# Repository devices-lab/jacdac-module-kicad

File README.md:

# jacdac-template-kicad

Jacdac RGB module KiCad project files for use as a template when creating new Jacdac modules. 

Based on Altium schematics from the [jacdac-ddk](https://github.com/jacdac/jacdac-ddk) and the [Jacdac KiCad library](https://github.com/mac-aron/jacdac-kicad).

#### Usage
- The script `library/convert.sh` can be used to download component symbols and footprints from LCSC (JLCPCB).
- The jobfile `export-fab-files.kicad_jobset` generates fabrication files to `gerbers/` with the correct settings
  - The column names in the CPL (component placement list) are incorrect for JLCPCB

Check the [neopixel-gerbersockets](../../tree/neopixel-gerbersockets) branch for a version with GerberSockets added.

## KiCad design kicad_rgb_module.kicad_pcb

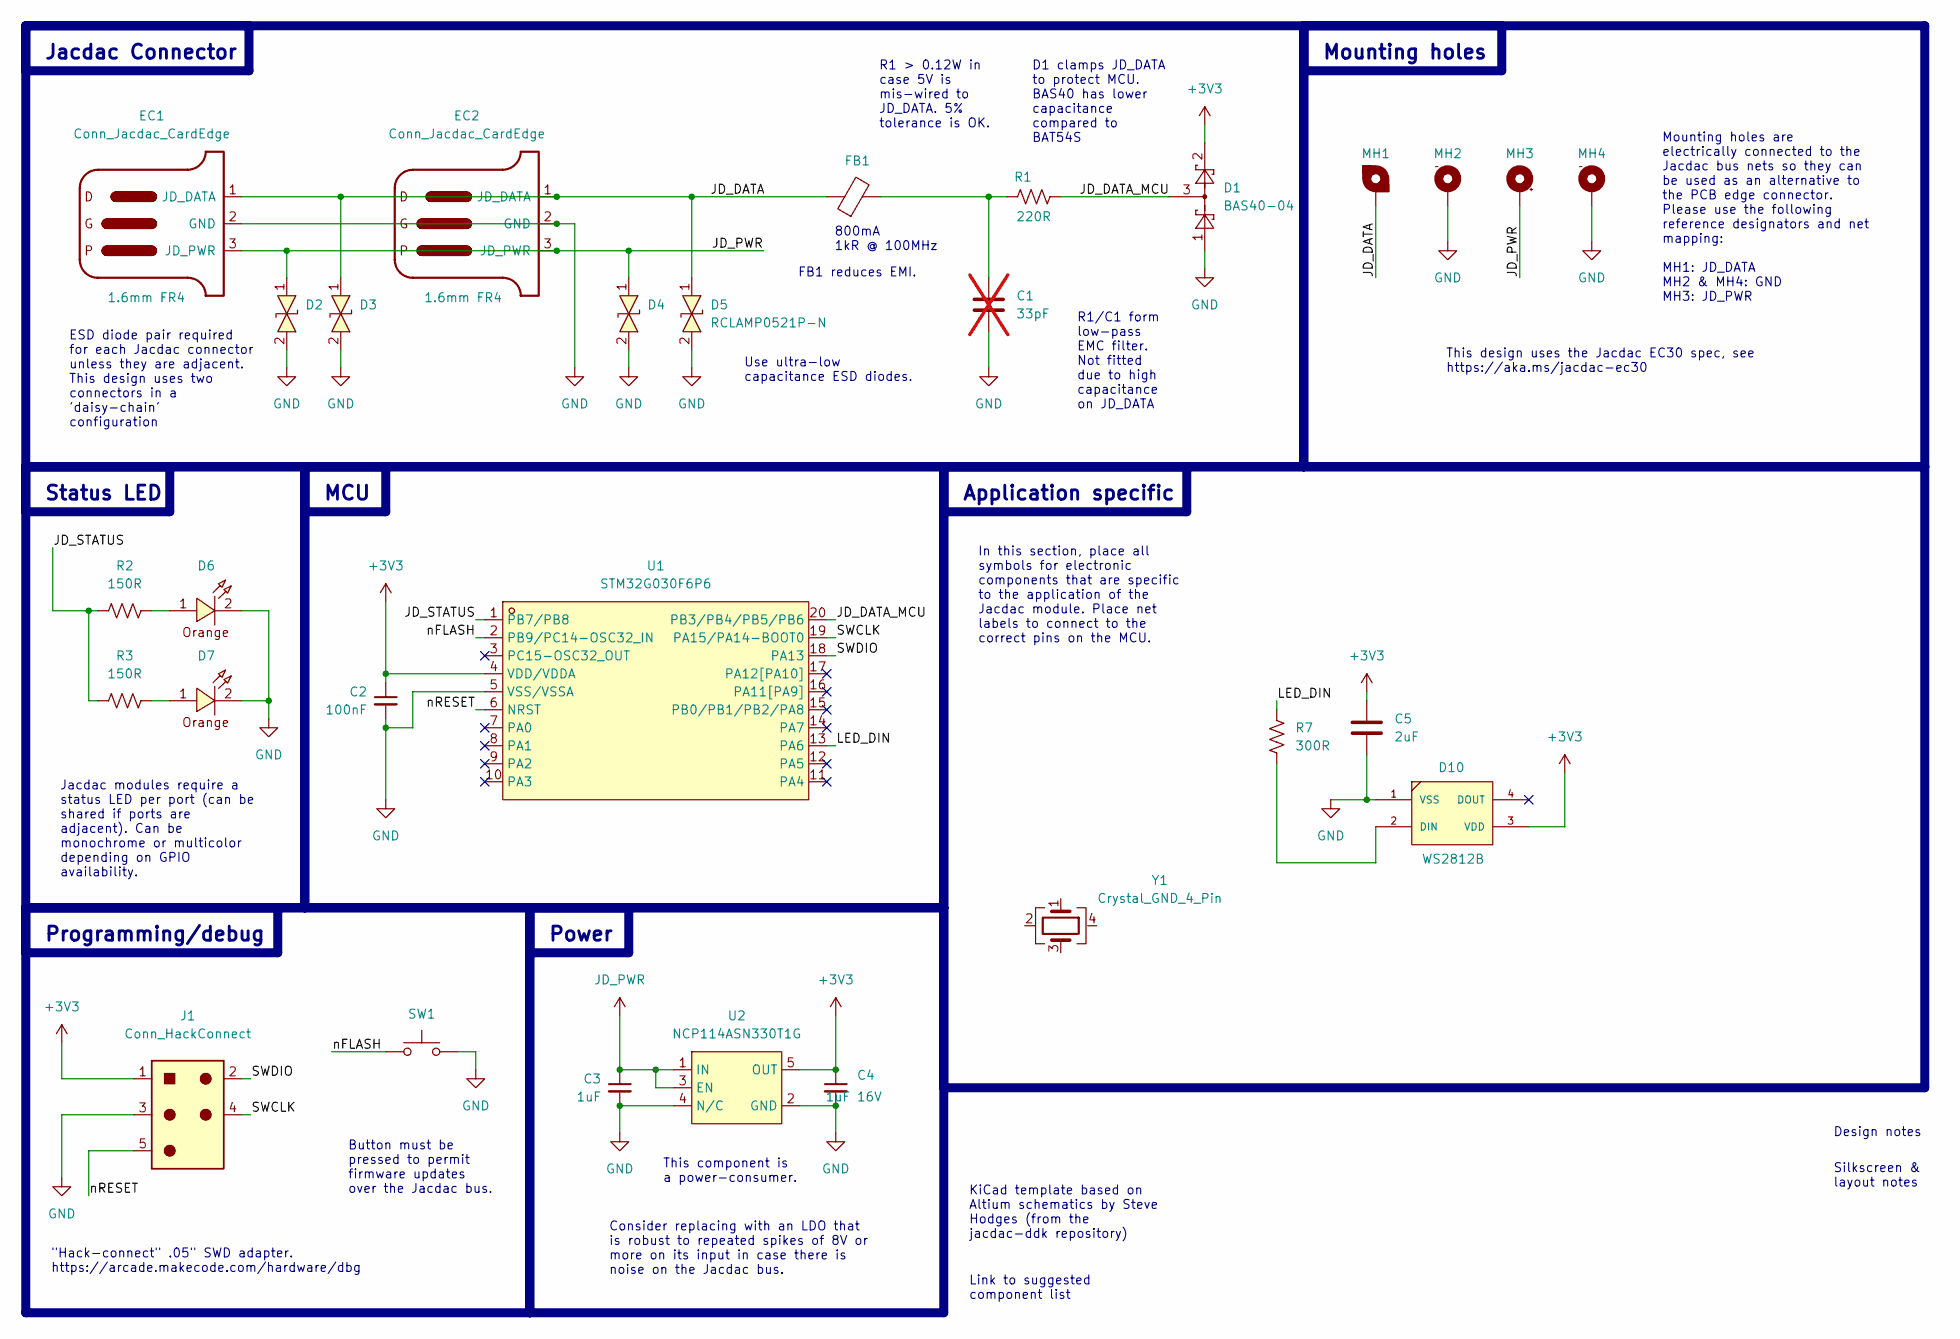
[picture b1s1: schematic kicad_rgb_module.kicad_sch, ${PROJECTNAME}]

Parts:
C1: 33pF; C_0603_1608Metric; LCSC Part C1663; not fitted
C2: 100nF; C_0603_1608Metric; LCSC Part C14663
C3: 1uF; C_0603_1608Metric; LCSC Part C15849
C4: 1uF 16V; C_0603_1608Metric; LCSC Part C15849
C5: 2uF; C_0603_1608Metric; LCSC Part C15849
D1: BAS40-04; SOT-23; LCSC Part C7502688
D2, D3, D4, D5: RCLAMP0521P-N; X1-DFN1006-2_L1.0-W0.6-P0.65-BI; LCSC Part C316043
D6, D7: SZYY0603O; LED0603-R-RD_ORANGE; LCSC Part C965800
D10: WS2812B; NeoPixel_WS2812B; Part type Extended; LCSC Part C2843785
EC1, EC2: Conn_Jacdac_CardEdge; JD-PEC-02_Prerouted_recessed
FB1: L0603; LCSC Part C1002
J1: Conn_HackConnect; HackConnect_P1.27mm
MH1: jacdac_hole_DATA_MH1
MH2: jacdac_hole_GND_MH2
MH3: jacdac_hole_PWR_MH3
MH4: jacdac_hole_GND_MH4
R1: 220R; R_0603_1608Metric; LCSC Part C22962
R2, R3: 150R; R_0603_1608Metric; LCSC Part C22808
R7: 300R; R_0603_1608Metric; LCSC Part C23025
SW1: TS-1088-AR02016; SW-SMD_L3.9-W3.0-P4.45; LCSC Part C720477
U1: STM32G030F6P6; TSSOP-20_L6.5-W4.4-P0.65-LS6.4-BL; LCSC Part C724040
U2: NCP114ASN330T1G; TSOP-5_L3.0-W1.5-P0.95-BL; LCSC Part C457666
Y1: Crystal_GND_4_Pin; Crystal_SMD_3225-4Pin_3.2x2.5mm; LCSC C5203640

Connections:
+3V3: C2.1, C4.1, C5.2, D1.2, D10.3 (VDD), J1.1, U1.4 (VDD/VDDA), U2.5 (OUT)
/JD_DATA: D3.1, D5.1, EC1.1 (JD_DATA), EC2.1 (JD_DATA), FB1.1, MH1.MH1
/JD_DATA_MCU: D1.3, R1.2, U1.20 (PB3/PB4/PB5/PB6)
/JD_STATUS: R2.1, R3.1, U1.1 (PB7/PB8)
/LED_DIN: R7.1, U1.13 (PA6)
/SWCLK: J1.4, U1.19 (PA15/PA14-BOOT0)
/SWDIO: J1.2, U1.18 (PA13)
/nFLASH: SW1.1, U1.2 (PB9/PC14-OSC32_IN)
/nRESET: J1.5, U1.6 (NRST)
GND: C1.2, C2.2, C3.2, C4.2, C5.1, D1.1, D2.2, D3.2, D4.2, D5.2, D6.2, D7.2, D10.1 (VSS), EC1.2 (GND), EC2.2 (GND), J1.3, MH2.MH2, MH4.MH4, SW1.2, U1.5 (VSS/VSSA), U2.2 (GND), U2.4 (N/C)
JD_PWR: C3.1, D2.1, D4.1, EC1.3 (JD_PWR), EC2.3 (JD_PWR), MH3.MH3, U2.1 (IN), U2.3 (EN)
unnamed: C1.1, FB1.2, R1.1
unnamed: D6.1, R2.2
unnamed: D7.1, R3.2
unnamed: D10.2 (DIN), R7.2
unnamed: Y1.2, Y1.4

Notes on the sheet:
Mounting holes
Status LED
Programming/debug
MCU
800mA 1kR @ 100MHz
Application specific
Power
Jacdac Connector
Use ultra-low capacitance ESD diodes.
D1 clamps JD_DATA to protect MCU. BAS40 has lower capacitance compared to BAT54S
This component is a power-consumer.
KiCad template based on Altium schematics by Steve Hodges (from the jacdac-ddk repository)
Jacdac modules require a status LED per port (can be shared if ports are adjacent). Can be monochrome or multicolor depending on GPIO availability.
Design notes
ESD diode pair required for each Jacdac connector unless they are adjacent. This design uses two connectors in a 'daisy-chain' configuration
Mounting holes are electrically connected to the Jacdac bus nets so they can be used as an alternative to the PCB edge connector. Please use the following reference designators and net mapping: MH1: JD_DATA MH2 & MH4: GND MH3: JD_PWR
Link to suggested component list
R1/C1 form low-pass EMC filter. Not fitted due to high capacitance on JD_DATA
This design uses the Jacdac EC30 spec, see https://aka.ms/jacdac-ec30
In this section, place all symbols for electronic components that are specific to the application of the Jacdac module. Place net labels to connect to the correct pins on the MCU.
Button must be pressed to permit firmware updates over the Jacdac bus.
FB1 reduces EMI.
Silkscreen & layout notes
R1 > 0.12W in case 5V is mis-wired to JD_DATA. 5% tolerance is OK.
Consider replacing with an LDO that is robust to repeated spikes of 8V or more on its input in case there is noise on the Jacdac bus.
"Hack-connect" .05" SWD adapter. https://arcade.makecode.com/hardware/dbg

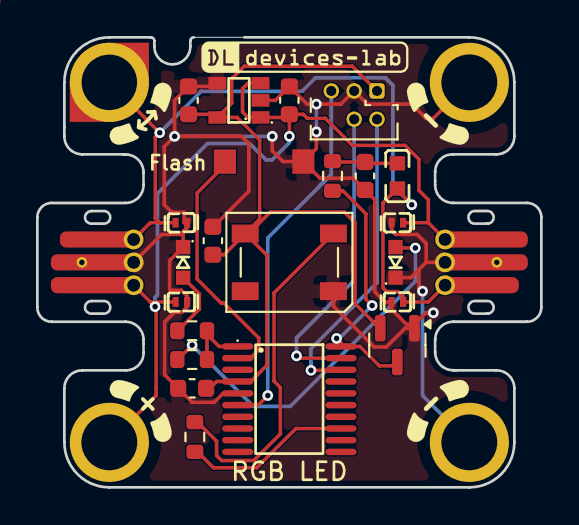
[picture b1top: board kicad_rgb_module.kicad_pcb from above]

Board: 2 copper layers, 28.0 x 25.0 mm, 28 parts (0 on the bottom side), 15 nets.
